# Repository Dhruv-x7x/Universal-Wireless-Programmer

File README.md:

<!-- DON'T MODIFY ANYTHING ABOVE -->
<!-- Modify from here -->
## 📄 Project Documentation

###  Project Name: Universal Wireless Programmer
###  Team Number: TUE-16
###  Team Members:

Anay Malviya 22b1255

Dhruv Meena 22b1279

Hardik Pratap Gohil 22b1293

Kaustav Saha 22b1228

Saptarshi Biswas 22b1258

---

### 📌 Problem Statement and Solution:

Whether it's deep inside big industrial machines, remote terrains or disaster zones, there is always bots and embedded devices to perform critical tasks and send back important data to the users. The big limitation here is that **we have to physically access them to reprogram them and download data.** The **Universal Wireless Programmer** completely cuts off all cords as well as this big limiation. We designed a **wireless programming** and **data retrieval** system for microcontrollers and development boards like Arduino Uno and ATmega328P. We use **RF communication** to send compiled code and receive real-time data back, all over-the-air.

---

### 📚 Contents

- [src](./src) – Source code including firmware and scripts
- [pcb](./pcb) – PCB design files and schematics
- [reports](./reports) – Milestone reports
- [others](./others) – Other circuit diagrams and misc. info
- [3d_models](./3d_models) – 3D CAD files
- [README.md](./README.md) – Problem Statement
- [bom.xls](./bom.xls) – Bill of Materials

---

### 💡 Learnings
We tried a lot of approaches throughout the project to figure out programming since there were no easily available resources related to that. Firstly, we got stuck at figuring out how to make arduino enter into the bootloader mode. For that we tried a bunch of approaches:
1) Software reset - Using DTR and RTS (Failed due to no response from arduino)
2) Power reset - Using pmos (Failed due to insufficient current to turn on the arduino)
3) Power reset - Using power mosfet (Reset worked but failed to enter bootloader mode)
4) Using reset pin - Reset worked but failed to enter bootloader mod

There were some more variations of these methods and some more approaches which all failed until we randomly figured out that the RESET PULSE DURATION which we found in the documentation and used without questioning was not sufficient and tuned it to a higher value which worked

We also spent a lot of time on figuring out USB CDC which was not working. In this task, we were supposed to figure out communication between STM in USB Host mode and arduino as a CDC device. We got no response from arduino whatsoever in this step, so we moved on to using UART for programming.

As soon as we received the RF PCB, we tested it and it was working completely fine. So we started working on implementing the SPI protocol to use the SI4464 PCB for wireless communication. We thought the issue was in software and spent a lot of time figuring out the configuration of the drivers. However, later we checked the hardware again and found a VDD-ground short. We believe that this was due to lack of ESD protection on the IC. We implemented our backup using bluetooth and are working on the PCB 

These were the difficulties we faced but we found out alternative ways to get each of them working to get to a working prototype.

---

*This project was completed as a part of EDL Lab in Spring'25*

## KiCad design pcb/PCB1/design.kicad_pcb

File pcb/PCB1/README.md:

## PCB for SI4464 Transceiver 

The **SI4464 PCB** is a **2** layered PCB we designed that acts like a breakout board for the [SI4464 IC](https://www.silabs.com/wireless/proprietary/ezradiopro-sub-ghz-ics/device.si4464?tab=specs). It can be subdivided into 2 major portions:

- **Matching Network**
- **Connections to Header Pins**

---

### Matching Network: 
 - It has a trace (of higher width) coming from the SMA connector (that is attached to the antenna), that goes into a series of inductors and capacitors (the matching network), and finally into the IC. The layout for the matching network was optimised, and was kept similar to the layout given in [layout guidelines](https://www.silabs.com/documents/public/application-notes/AN629.pdf) for the IC.
 - **Decoupling capacitors** were also placed very close to the IC power input ports, as per the layout guidelines.
 - All the traces in these portions were made on the **front copper layer**.

### Header Pins for External Connection:
- We attached this PCB on the STM32 Nucleo-Board which blocked its pins and hence made a separate set of header pins on the top that were shorted to the original Nucleo board pins so that the pins underneath could be accessed from these.
- 2 traces for the connection of the header pin to the IC were done in the **bottom copper layer**.

### Directory Structure

```plaintext
  ├── /PCB1 
    ├── design.kicad_pcb # PCB Design in KiCAD format 
    ├── schematic.sch # KiCAD Schematic
    ├── README.md
    ├── pictures
      ├── ALL_LAYERS_PCB.jpg # Schematic from front
      ├── pcb_board.jpg # PCB Board without antenna
      ├── pcb_with_antenna.jpg # PCB Board with antenna
      ├── pcb_3d_front.jpeg # 3D view from front
      ├── pcb_3d_back # 3D view from back
      ├── pcb_sch_back.jpeg  # Schematic from back
```

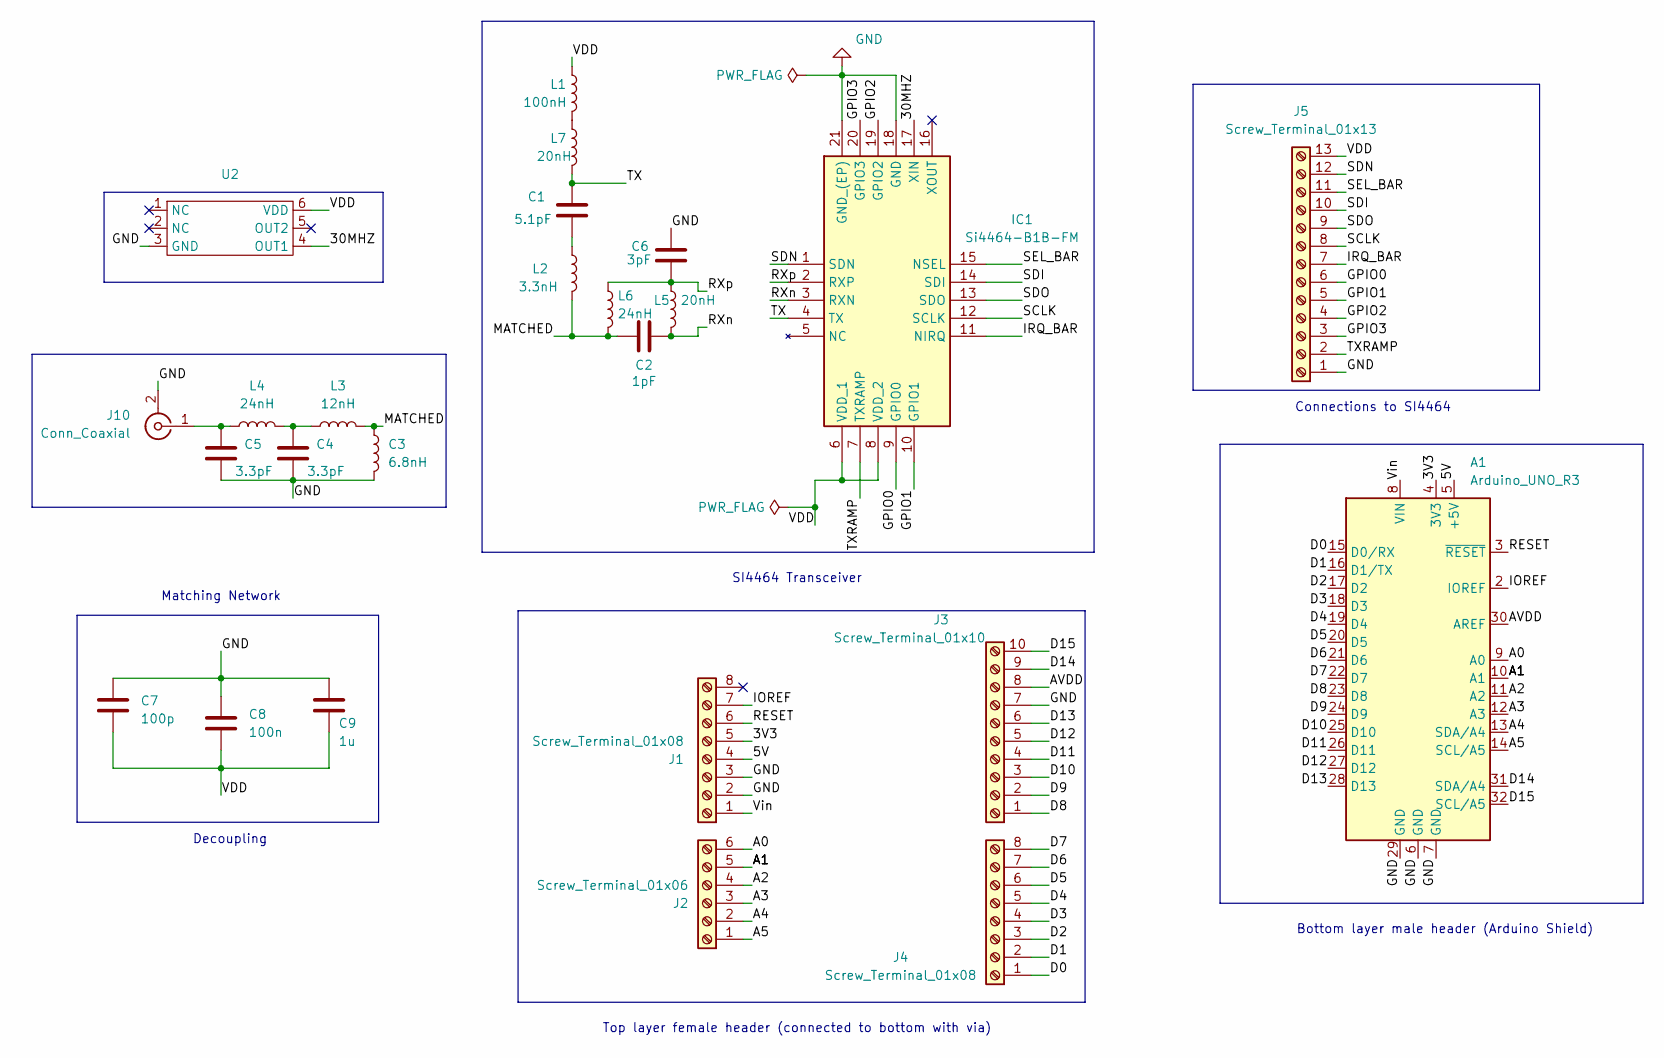
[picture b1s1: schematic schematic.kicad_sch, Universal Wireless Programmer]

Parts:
A1: Arduino_UNO_R3
C1: 5.1pF; C_0603_1608Metric_Pad1.08x0.95mm_HandSolder
C2: 1pF; C_0603_1608Metric_Pad1.08x0.95mm_HandSolder
C3: 6.8nH; L_0603_1608Metric_Pad1.05x0.95mm_HandSolder
C4, C5: 3.3pF; C_0402_1005Metric_Pad0.74x0.62mm_HandSolder
C6: 3pF; C_0603_1608Metric_Pad1.08x0.95mm_HandSolder
C7: 100p; C_0402_1005Metric_Pad0.74x0.62mm_HandSolder
C8: 100n; C_0603_1608Metric_Pad1.08x0.95mm_HandSolder
C9: 1u; C_0402_1005Metric_Pad0.74x0.62mm_HandSolder
IC1: Si4464-B1B-FM; QFN50P400X400X90-21N; Mouser Part Number 634-SI4464-B1X-FM
J1, J4: Screw_Terminal_01x08; PinSocket_1x08_P2.54mm_Vertical
J2: Screw_Terminal_01x06; PinSocket_1x06_P2.54mm_Vertical
J3: Screw_Terminal_01x10; PinSocket_1x10_P2.54mm_Vertical
J5: Screw_Terminal_01x13; PinSocket_1x13_P2.54mm_Vertical
J10: Conn_Coaxial; SMA_Amphenol_132289_EdgeMount
L1: 100nH; L_0603_1608Metric_Pad1.05x0.95mm_HandSolder
L2: 3.3nH; L_0603_1608Metric_Pad1.05x0.95mm_HandSolder
L3: 12nH; L_0603_1608Metric_Pad1.05x0.95mm_HandSolder
L4, L6: 24nH; L_0603_1608Metric_Pad1.05x0.95mm_HandSolder
L5, L7: 20nH; L_0603_1608Metric_Pad1.05x0.95mm_HandSolder
U2: Oscillator_SMD_IDT_JS6-6_5.0x3.2mm_P1.27mm

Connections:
/3V3: A1.4 (3V3), J1.5
/5V: A1.5 (+5V), J1.4
/30MHZ: IC1.17 (XIN), U2.4 (OUT1)
/A0: A1.9 (A0), J2.6
/A1: A1.10 (A1), J2.5
/A2: A1.11 (A2), J2.4
/A3: A1.12 (A3), J2.3
/A4: A1.13 (SDA/A4), J2.2
/A5: A1.14 (SCL/A5), J2.1
/AVDD: A1.30 (AREF), J3.8
/D0: A1.15 (D0/RX), J4.1
/D1: A1.16 (D1/TX), J4.2
/D2: A1.17 (D2), J4.3
/D3: A1.18 (D3), J4.4
/D4: A1.19 (D4), J4.5
/D5: A1.20 (D5), J4.6
/D6: A1.21 (D6), J4.7
/D7: A1.22 (D7), J4.8
/D8: A1.23 (D8), J3.1
/D9: A1.24 (D9), J3.2
/D10: A1.25 (D10), J3.3
/D11: A1.26 (D11), J3.4
/D12: A1.27 (D12), J3.5
/D13: A1.28 (D13), J3.6
/D14: A1.31 (SDA/A4), J3.9
/D15: A1.32 (SCL/A5), J3.10
/GPIO0: IC1.9 (GPIO0), J5.6
/GPIO1: IC1.10 (GPIO1), J5.5
/GPIO2: IC1.19 (GPIO2), J5.4
/GPIO3: IC1.20 (GPIO3), J5.3
/IOREF: A1.2 (IOREF), J1.7
/IRQ_BAR: IC1.11 (NIRQ), J5.7
/MATCHED: C2.1, C3.1, L2.2, L3.2, L6.2
/RESET: A1.3 (~RESET), J1.6
/RXn: C2.2, IC1.3 (RXN), L5.2
/RXp: C6.2, IC1.2 (RXP), L5.1, L6.1
/SCLK: IC1.12 (SCLK), J5.8
/SDI: IC1.14 (SDI), J5.10
/SDN: IC1.1 (SDN), J5.12
/SDO: IC1.13 (SDO), J5.9
/SEL_BAR: IC1.15 (NSEL), J5.11
/TX: C1.1, IC1.4 (TX), L7.2
/TXRAMP: IC1.7 (TXRAMP), J5.2
/VDD: C7.2, C8.2, C9.2, IC1.6 (VDD_1), IC1.8 (VDD_2), J5.13, L1.1, U2.6 (VDD)
/Vin: A1.8 (VIN), J1.1
GND: A1.6 (GND), A1.7 (GND), A1.29 (GND), C3.2, C4.2, C5.2, C6.1, C7.1, C8.1, C9.1, IC1.18 (GND), IC1.21 (GND_(EP)), J1.2, J1.3, J3.7, J5.1, J10.2 (Ext), U2.3 (GND)
unnamed: C1.2, L2.1
unnamed: C4.1, L3.1, L4.2
unnamed: C5.1, J10.1 (In), L4.1
unnamed: L1.2, L7.1

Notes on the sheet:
Connections to SI4464
Decoupling
Top layer female header (connected to bottom with via)
Bottom layer male header (Arduino Shield)
SI4464 Transceiver
Matching Network

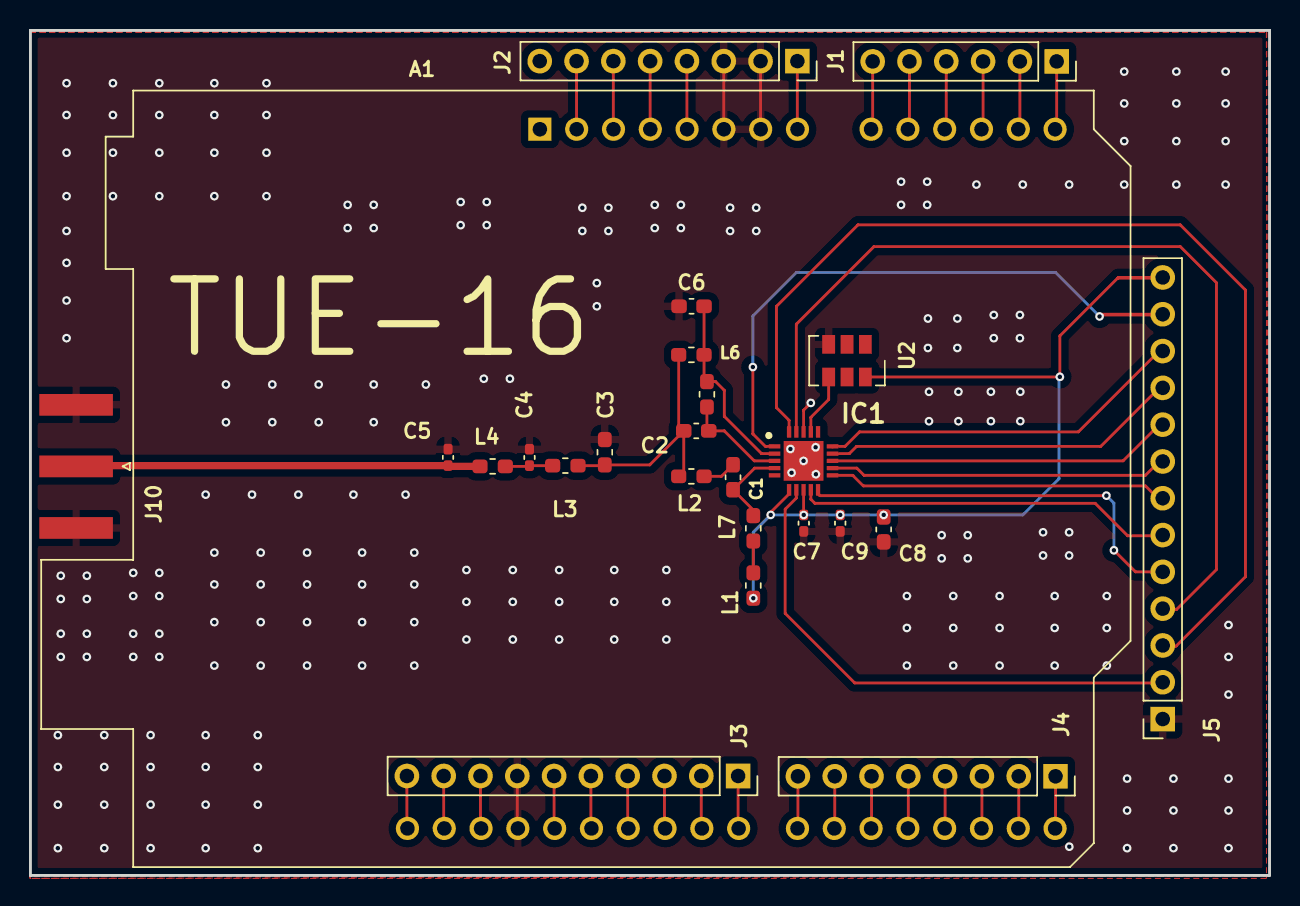
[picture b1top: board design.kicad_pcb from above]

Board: 2 copper layers, 85.5 x 58.3 mm, 25 parts (0 on the bottom side), 50 nets.

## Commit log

2025-08-17 project-edl
